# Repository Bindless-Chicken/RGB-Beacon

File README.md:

<h1 align=center>
   
    <br>
    RGB Beacon
    <br>
</h1>

The RGB Beacon is a small hackable RGB LED based on the ATTiny13a. In addition to a undeniably funky LED, the beacon also integrate a tactile switch and a potentiometer for even more goodness.

## Hardware

### Bill of materials

The MCU inside the Beacon is a [ATTiny13a](http://www.atmel.com/Images/doc8126.pdf) clocked at 9.6MHz using the onboard oscillator.

The RGB LED is the common anode [ASMB-MTB1-0A3A2](https://docs.broadcom.com/docs/AV02-4194EN).

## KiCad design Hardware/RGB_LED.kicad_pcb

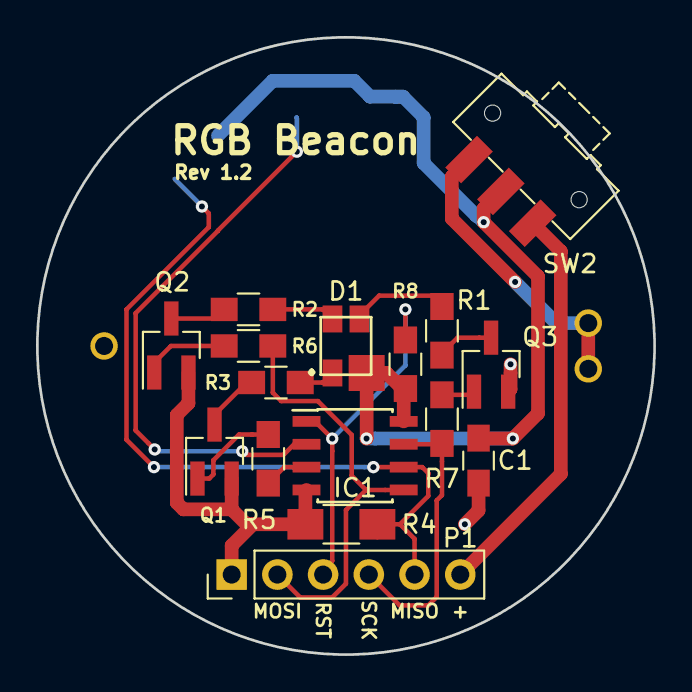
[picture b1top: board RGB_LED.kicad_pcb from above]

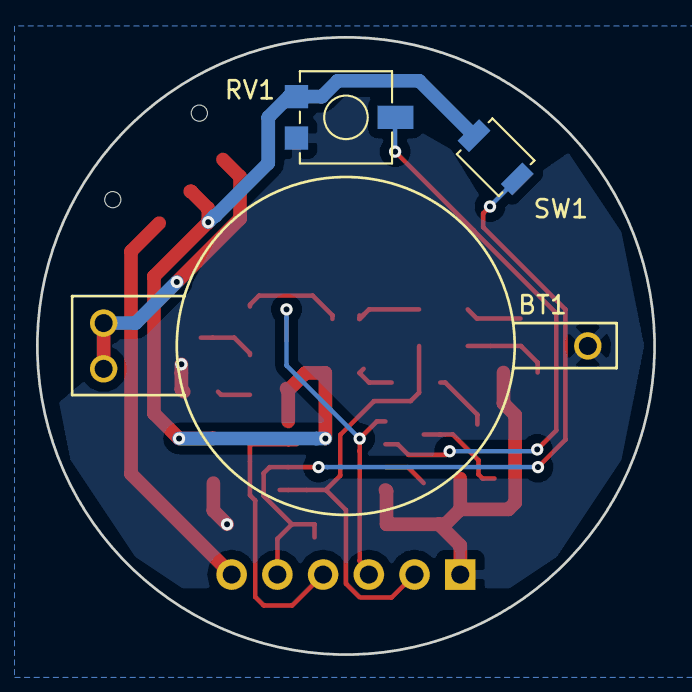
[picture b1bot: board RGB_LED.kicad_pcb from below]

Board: 2 copper layers, 34.3 x 34.3 mm, 19 parts (3 on the bottom side), 19 nets.

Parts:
BT1: Battery; HU2032-LF
C1: 0.1uF; C_0805_HandSoldering
D1: LED_RABG_2; ASMB-MTB1-0A3A2
IC1: ATTINY13A-SS; SOIC-8_3.9x4.9mm_Pitch1.27mm
P1: CONN_01X06; Socket_Strip_Straight_1x06_Pitch2.54mm
Q1, Q2, Q3: MMBT3904; SOT-23_Handsoldering
R1, R2: 8; R_0805_HandSoldering
R3: 36; R_0805_HandSoldering
R4: 10k; R_1206_HandSoldering
R5, R6, R7: 7k2; R_0805_HandSoldering
R8: 10k; R_0805_HandSoldering
RV1: POT; Potentiometer_Trimmer_Vishay_TS53YL
SW1: SW_PUSH; SW_SPST_B3U-1000P
SW2: Switch_SPDT_x2; SW_SPDT_CK-JS102011SAQN

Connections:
+3V3: C1.1, D1.4, IC1.8, R8.1, RV1.3, SW1.1, SW2.2
/Blue: IC1.7, P1.4, R7.1
/Green: IC1.5, P1.2, R6.1
/ICP_PWR: P1.6, SW2.1
/Red: IC1.3, R5.1
/Switch: IC1.6, P1.5, R4.2, SW1.2
/Trim: IC1.2, RV1.2
GND: BT1.2, C1.2, IC1.4, P1.1, Q1.2, Q2.2, Q3.2, R4.1, RV1.1
unnamed: BT1.1, SW2.3
unnamed: D1.1, R3.2
unnamed: D1.2, R2.2
unnamed: D1.3, R1.2
unnamed: IC1.1, P1.3, R8.2
unnamed: Q1.1, R5.2
unnamed: Q1.3, R3.1
unnamed: Q2.1, R6.2
unnamed: Q2.3, R2.1
unnamed: Q3.1, R7.2
unnamed: Q3.3, R1.1

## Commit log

2017-10-05 Commit Hardware
2017-10-05 Software dump
    Very WIP, much in progress
2017-10-06 Readme
2017-10-08 Add decoupling cap
    Fix #1
2017-10-15 Extract pinout better & color
2017-11-26 Switch sources to c
2017-11-27 Board rev 1.2
    + Add 10k resistor to reset
    + Switch and trim moved to back for better ux
